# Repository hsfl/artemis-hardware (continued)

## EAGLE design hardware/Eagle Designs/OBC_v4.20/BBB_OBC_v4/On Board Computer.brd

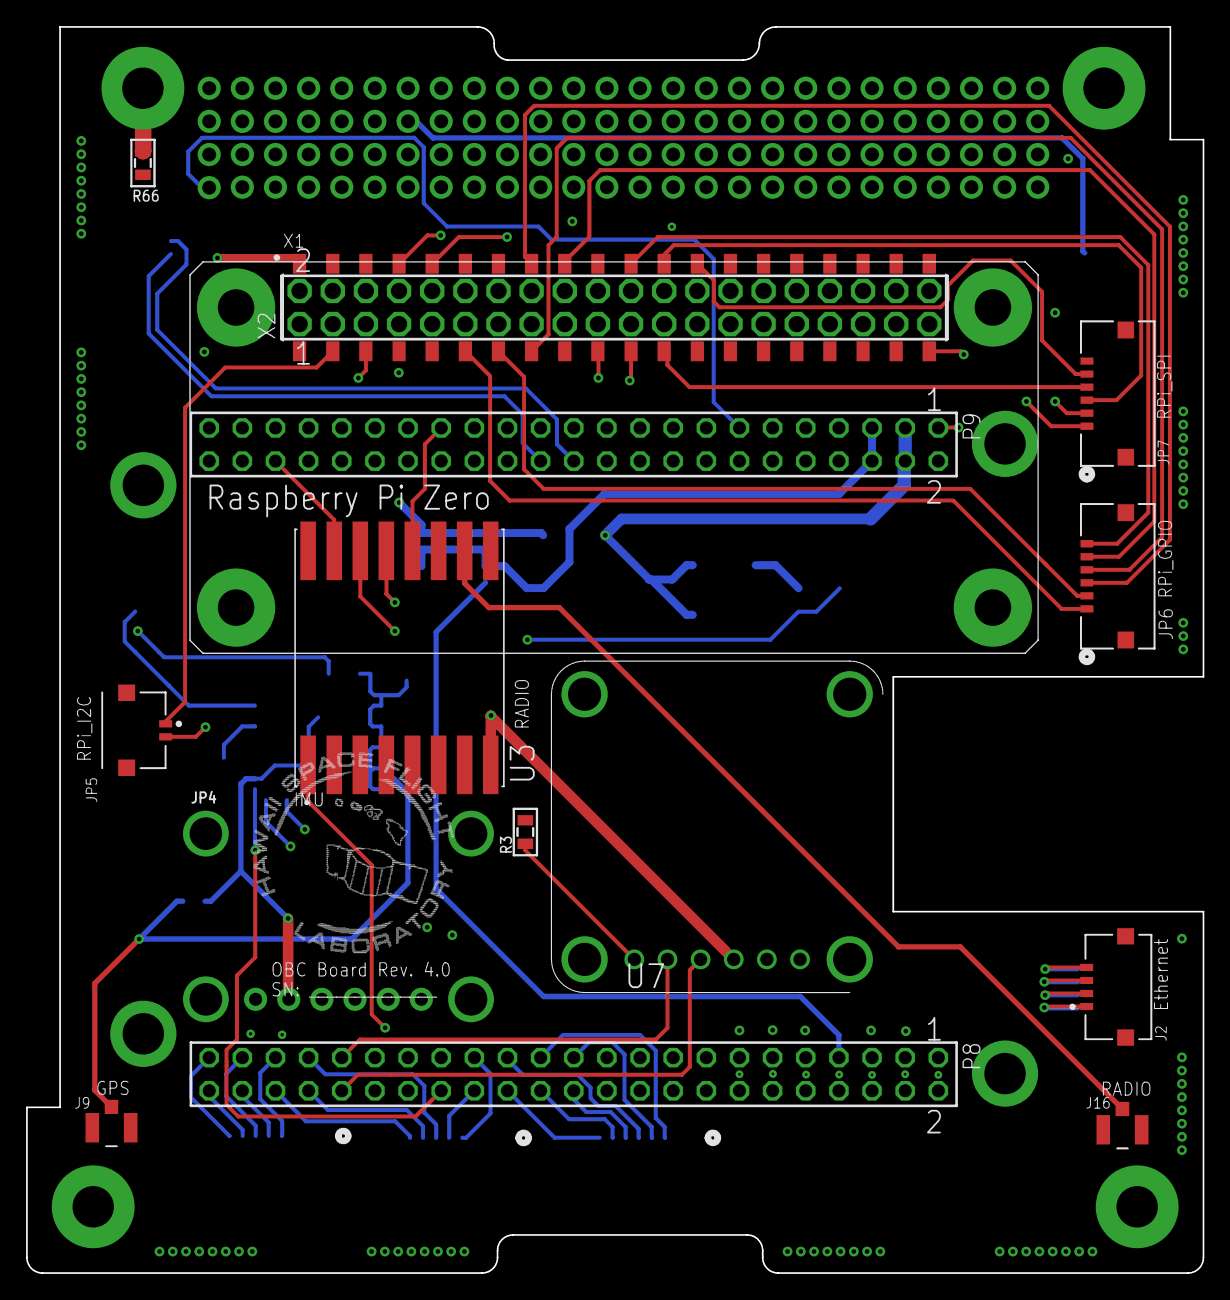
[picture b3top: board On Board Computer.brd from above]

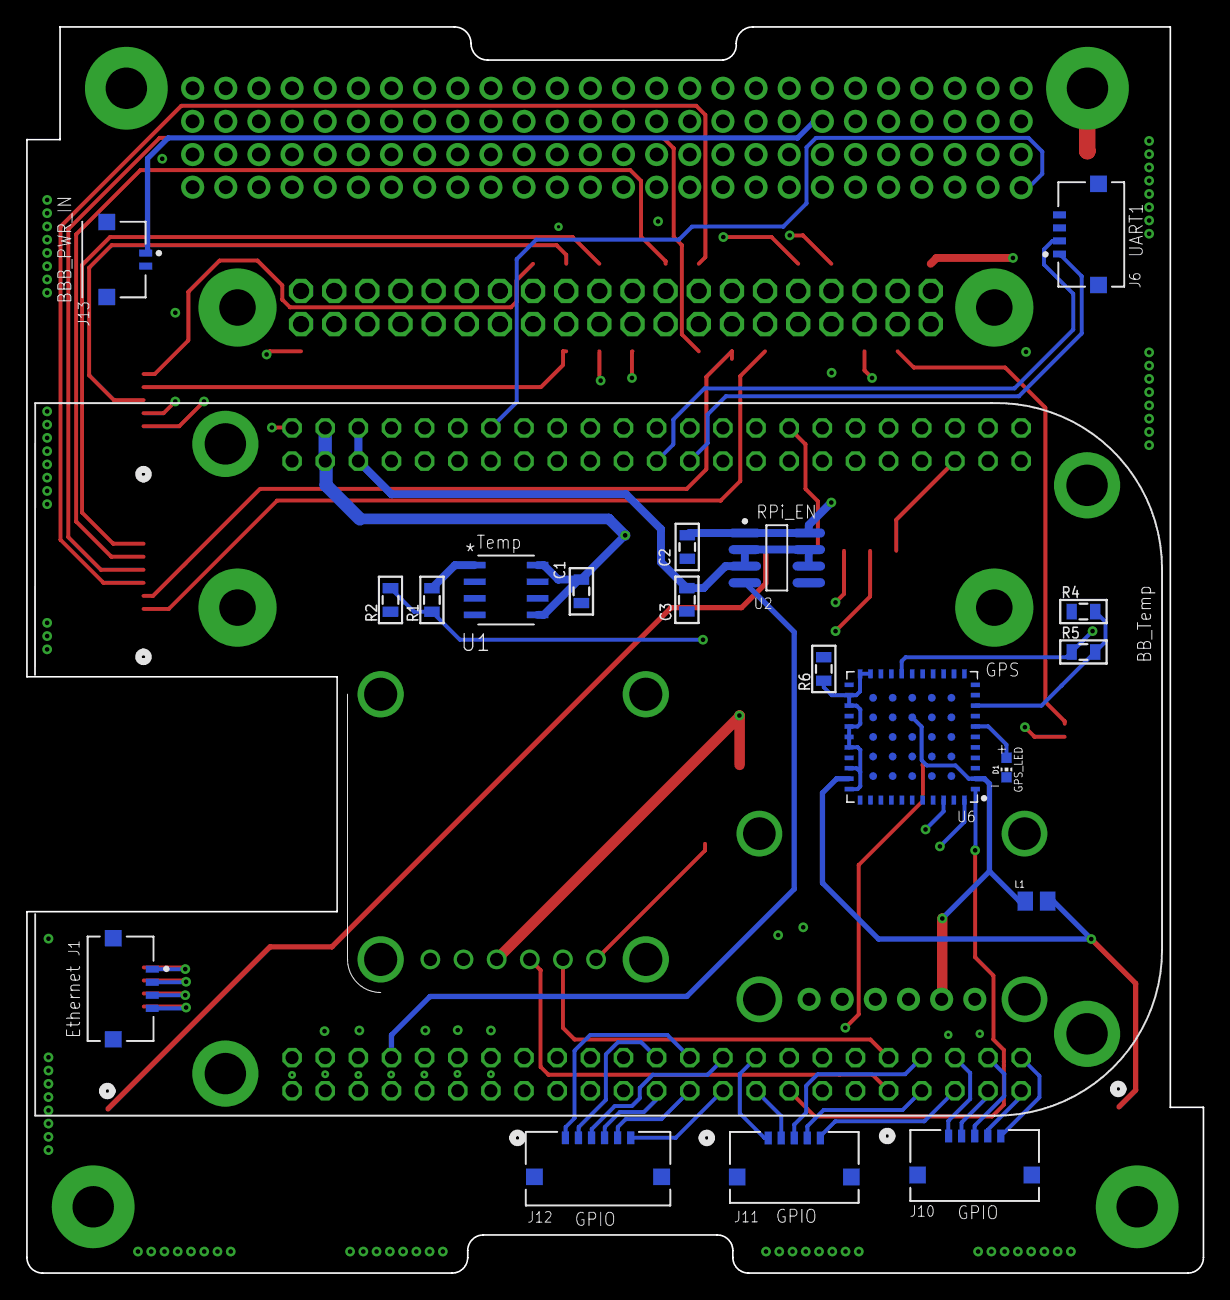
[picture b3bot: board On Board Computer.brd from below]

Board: 4 copper layers, 90.2 x 95.5 mm, 35 parts (19 on the bottom side), 72 nets.

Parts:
C1: .1uF; 0805
C2, C3: 1uF; 0805
D1: CHIP-LED0603
H1: PC104_WCONN
J1, J2, J6: MOLEX_503763-0491MOLEX_503763-0491_0_0; MOLEX_503763-0491_0
J9, J16: U.FL-R-SMT-1(01); CONN_-SMT-1(01)
J10, J11: 503763-0591; CONN_5037630591_MOL
J12: 503763-0691; CONN_503763-0691_MOL
J13: MOLEX_503763-0291MOLEX_503763-0291_0_0; MOLEX_503763-0291_0
JP4: 1X06_ROUND_70
JP5: MOLEX_503763-0291MOLEX_503763-0291_0_0; MOLEX_503763-0291_0
JP6, JP7: 503763-0691; CONN_503763-0691_MOL
L1: L; INDC2012X145N
P8, P9: SSW-123-02-G-D
R1: 27k; 0805
R2, R3: 10k; 0805
R4, R5, R6: 0; 0805
R66: 1M; 0805
U1: TMP36FSZR_8_ADI-L; R_8_ADI-L
U2: LTC1477CS8LINEAR_TECHNOLOGY_LTC1477CS8_0_2; LINEAR_TECHNOLOGY_LTC1477CS8_2
U3: RFM69HCW_433_900; RFM69HCW_433
U6: ORION_A38LORION_A38L; ORION_A38L
U7: PA1010D
X1: C25582-40G-M36-0A; ADAFRUIT_C25582-40G-M36-0A_0
X2: SSW-120-02-G-D

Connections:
3V3_BUS: H1.2.27, H1.2.28, R5.1, U6.18
5V_BUS: H1.2.25, H1.2.26
+3V3_VCC: C1.1, JP4.2, L1.1, P9.3, P9.4, U1.5, U1.8, U3.16, U6.2, U6.58, U7.3
+5V_VCC: C3.1, P9.5, P9.6, U2.2, U2.3, U2.6, U2.7
AIN0: P9.39, R1.1, R2.2
AIN1: H1.1.3, P9.40
AIN2: H1.1.4, P9.37
AIN3: H1.1.5, P9.38
AIN4: H1.1.6, P9.33
AIN5: H1.1.7, P9.36
AIN6: H1.1.8, P9.35
BUS_UART4_RXD(BBB_TX): H1.1.1, P9.13
BUS_UART4_TXD(BBB_RX): H1.1.2, P9.11
GND: C1.2, C2.2, C3.2, D1.C, H1.2.7, H1.2.14, H1.2.17, H1.2.21, H1.2.22, H1.2.29, H1.2.30, H1.2.32, H1.2.47, H1.2.48, J1.5, J1.6, J2.5, J2.6, J6.3, J6.4, J6.5, J6.6, J9.1, J9.2, J10.6, J10.7, J11.6, J11.7, J12.7, J12.8, J13.2, J13.3, J13.4, J16.1, J16.2, JP4.3, JP5.3, JP5.4, JP6.7, JP6.8, JP7.6, JP7.7, JP7.8, P8.1, P8.2, P9.1, P9.2, R2.1, R3.2, R4.1, R6.2, R66.2, U1.4, U2.5, U3.6, U3.8, U6.10, U6.11, U6.15, U6.19, U6.64, U7.1, X1.39
GPIO1_0: J12.1, P8.25
GPIO1_1: J12.4, P8.24
GPIO1_4: J12.2, P8.23
GPIO1_29: J12.5, P8.26
GPIO2_6: J10.5, P8.45
GPIO2_7: J10.4, P8.46
GPIO2_8: J10.3, P8.43
GPIO2_9: J10.2, P8.44
GPIO2_10: J10.1, P8.41
GPIO2_11: J11.5, P8.42
GPIO2_12: J11.3, P8.39
GPIO2_13: J11.4, P8.40
GPIO2_22: J12.3, P8.27
GPIO2_23: J11.1, P8.29
GPIO2_24: J12.6, P8.28
GPIO2_25: J11.2, P8.30
GPIO17: JP6.1, X1.11
GPIO22: JP6.4, X1.15
GPIO23: JP6.3, X1.16
GPIO24: JP6.5, X1.18
GPIO25: JP6.6, X1.22
GPIO27: JP6.2, X1.13
GPS_RSTN: P8.32, U6.1
I2C2_SCL: JP4.4, P9.19
I2C2_SDA: JP4.5, P9.20
unnamed: J16.3, U3.7
unnamed: R1.2, U1.1
unnamed: R4.2, R5.2, U6.9
unnamed: J9.3, L1.2, U6.32
unnamed: R3.1, U7.6
unnamed: D1.A, U6.7
unnamed: H1.P$4, R66.1
RADIO_RESET: P8.36, U3.9
RF_GND: R6.1, U6.21, U6.22, U6.24, U6.25, U6.27, U6.28, U6.29, U6.31, U6.33
RPI_5V_PWR_IN: C2.1, U2.1, U2.8, X1.2
RPI_ENABLE: P8.7, U2.4
RX+: J1.3, J2.2
RX-: J1.4, J2.1
SCL1_I2C: JP5.2, X1.5
SDA1_I2C: JP5.1, X1.3
SPI0_CE0_N: JP7.3, X1.24
SPI0_CE1_N: JP7.5, X1.26
SPI0_MISO: JP7.2, X1.21
SPI0_MOSI: JP7.1, X1.19
SPI0_SCLK: JP7.4, X1.23
SPI1_CS1: P9.42, U3.2
SPI1_D0: P9.29, U3.4
SPI1_D1: P9.30, U3.3
SPI1_SCLK: P9.31, U3.5
SW_5V_1: H1.2.13, J13.1
TX+: J1.1, J2.4
TX-: J1.2, J2.3
UART1_RXD: J6.1, P9.26
UART1_TXD: J6.2, P9.24
UART2_RXD: P9.22, X1.8
UART2_TXD: P9.21, X1.10
UART5_RXD: P8.38, U6.44, U7.4
UART5_TXD: P8.37, U6.42, U7.5

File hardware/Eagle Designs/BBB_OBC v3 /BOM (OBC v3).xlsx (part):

Part | Value | Device | Package | Description | AUTOMOTIVE | AVAILABILITY | BUILT_BY | CENTROID_NOT_SPECIFIED | CIIVA_IDS | COMPONENT_LINK_1_DESCRIPTION | COMPONENT_LINK_1_URL | COMPONENT_LINK_3_DESCRIPTION | COMPONENT_LINK_3_URL | CONN_GENDER | CONN_ORIENTATION | CONTACT_MATERIAL | COPYRIGHT | CURRENT_RATING | DATASHEET | DESCRIPTION | DEVICE_CLASS_L1 | DEVICE_CLASS_L2 | DEVICE_CLASS_L3 | DIGIKEY_DESCRIPTION | DIGIKEY_PART_NUMBER | FOOTPRINT_URL | FOOTPRINT_VARIANT_NAME_0 | FOOTPRINT_VARIANT_NAME_1 | FOOTPRINT_VARIANT_NAME_2 | HEIGHT | IMPORTED | IMPORTED_FROM | IMPORT_TS | LEAD_FREE | MANUFACTURER_PART_NUMBER | MF | MFG_PACKAGE_IDENT | MFG_PACKAGE_IDENT_DATE | MFG_PACKAGE_IDENT_REV | MFR_NAME | MOUNTING_TECHNOLOGY | MOUSER_PART_NUMBER | MP | MPN | NUMBER_OF_CONTACTS | NUMBER_OF_ROWS | OC_FARNELL | OC_NEWARK | PACKAGE | PACKAGE_DESCRIPTION | PACKAGE_VERSION | PITCH | POPULARITY | PREFIX | PRICE | RELEASE_DATE | ROHS | SOURCELIBRARY | TEMPERATURE_RANGE_HIGH | TEMPERATURE_RANGE_LOW | VAULT_GUID | VAULT_REVISION | VENDOR | VERIFICATION_VERSION | VOLTAGE_RATING
3V3_BUS |  | 1,6/0,9 | 1,6/0,9 | THROUGH-HOLE PAD |  |  |  |  |  |  |  |  |  |  |  |  |  |  |  |  |  |  |  |  |  |  |  |  |  |  |  |  |  |  |  |  |  |  |  |  |  |  |  |  |  |  |  |  |  |  |  |  | 7.0
C1 | .1uF | CAP0805 | 805.0 | Capacitor
C2 | 1uF | CAP0805 | 805.0 | Capacitor
C3 | 1uF | CAP0805 | 805.0 | Capacitor
D1 |  | LEDCHIP-LED0603 | CHIP-LED0603 | LED |  |  |  |  |  |  |  |  |  |  |  |  |  |  |  |  |  |  |  |  |  |  |  |  |  |  |  |  |  |  |  |  |  |  |  |  |  |  |  |  |  |  |  |  |  |  |  |  | 26.0
GND | GND | 1,6/0,9 | 1,6/0,9 | THROUGH-HOLE PAD |  |  |  |  |  |  |  |  |  |  |  |  |  |  |  |  |  |  |  |  |  |  |  |  |  |  |  |  |  |  |  |  |  |  |  |  |  |  |  |  |  |  |  |  |  |  |  |  | 7.0
GPS_BOOTSEL |  | 1,6/0,9 | 1,6/0,9 | THROUGH-HOLE PAD |  |  |  |  |  |  |  |  |  |  |  |  |  |  |  |  |  |  |  |  |  |  |  |  |  |  |  |  |  |  |  |  |  |  |  |  |  |  |  |  |  |  |  |  |  |  |  |  | 7.0
H1 | SSQ-126-22-G-D | SSQ-126-22-G-D |  | Large PC104 receptacle |  |  |  |  |  |  |  |  |  |  |  |  |  |  | https://www.mouser.com/datasheet/2/527/ssq_th-1370157.pdf
H2 | SSQ-126-22-G-D | SSQ-126-22-G-D |  | Large PC104 receptacle |  |  |  |  |  |  |  |  |  |  |  |  |  |  | https://www.mouser.com/datasheet/2/527/ssq_th-1370157.pdf
J1 | MOLEX_503763-0491MOLEX_503763-0491_0_0 | MOLEX_503763-0491MOLEX_503763-0491_0_0 | MOLEX_503763-0491_0 | Wire-To-Board Connector, Pico-Lock 503763 Series, Surface Mount, Header, 4 Cont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 | No |  |  | No |  |  |  |  |  | Male | Right Angle | Gold,Nickel |  | 1.5A | https://www.molex.com/webdocs/datasheets/pdf/en-us/503763049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 |  | Connectors | Headers and Wire Housings | unset | CONN HEADER 1MM R/A 4CKT | WM10655CT-ND | https://www.molex.com/pdm_docs/sd/5037630491_sd.pdf | Recommended_Land_Pattern |  |  | 1.7mm |  |  |  | Yes |  | Molex | 503763-0491 | 0.0 | 0.0 |  |  | 538-503763-0491 |  | 503763-0491 | 4.0 | 1.0 |  |  | HDR4 |  |  | 1mm |  | J |  |  | Yes |  | +105°C | -40°C |  |  |  | 0.0.0.1 | 150V
J2 | MOLEX_503763-0491MOLEX_503763-0491_0_0 | MOLEX_503763-0491MOLEX_503763-0491_0_0 | MOLEX_503763-0491_0 | Wire-To-Board Connector, Pico-Lock 503763 Series, Surface Mount, Header, 4 Cont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 | No |  |  | No |  |  |  |  |  | Male | Right Angle | Gold,Nickel |  | 1.5A | https://www.molex.com/webdocs/datasheets/pdf/en-us/503763049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 |  | Connectors | Headers and Wire Housings | unset | CONN HEADER 1MM R/A 4CKT | WM10655CT-ND | https://www.molex.com/pdm_docs/sd/5037630491_sd.pdf | Recommended_Land_Pattern |  |  | 1.7mm |  |  |  | Yes |  | Molex | 503763-0491 | 0.0 | 0.0 |  |  | 538-503763-0491 |  | 503763-0491 | 4.0 | 1.0 |  |  | HDR4 |  |  | 1mm |  | J |  |  | Yes |  | +105°C | -40°C |  |  |  | 0.0.0.1 | 150V
J6 | MOLEX_503763-0491MOLEX_503763-0491_0_0 | MOLEX_503763-0491MOLEX_503763-0491_0_0 | MOLEX_503763-0491_0 | Wire-To-Board Connector, Pico-Lock 503763 Series, Surface Mount, Header, 4 Cont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 | No |  |  | No |  |  |  |  |  | Male | Right Angle | Gold,Nickel |  | 1.5A | https://www.molex.com/webdocs/datasheets/pdf/en-us/503763049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 |  | Connectors | Headers and Wire Housings | unset | CONN HEADER 1MM R/A 4CKT | WM10655CT-ND | https://www.molex.com/pdm_docs/sd/5037630491_sd.pdf | Recommended_Land_Pattern |  |  | 1.7mm |  |  |  | Yes |  | Molex | 503763-0491 | 0.0 | 0.0 |  |  | 538-503763-0491 |  | 503763-0491 | 4.0 | 1.0 |  |  | HDR4 |  |  | 1mm |  | J |  |  | Yes |  | +105°C | -40°C |  |  |  | 0.0.0.1 | 150V
J9 | U.FL-R-SMT-1(01) | U.FL-R-SMT-1(01) | CONN_-SMT-1(01) |  |  |  | EMA_Matt |  |  |  |  |  |  |  |  |  | Copyright (C) 2018 Accelerated Designs. All rights reserved |  |  |  |  |  |  |  |  |  |  |  |  |  |  |  |  |  | U.FL-R-SMT-1(01) |  |  |  |  |  |  |  |  |  |  |  |  |  |  |  |  |  |  |  |  |  |  | Hirose_12_20_2019 |  |  |  |  | Hirose
J10 | 503763-0591 | 503763-0591 | CONN_5037630591_MOL |  |  |  | EMA_Cory |  |  |  |  |  |  |  |  |  | Copyright (C) 2018 Accelerated Designs. All rights reserved |  | https://www.molex.com/pdm_docs/sd/5037630591_sd.pdf |  |  |  |  |  |  |  |  |  |  |  |  |  |  |  | 503763-0591 |  |  |  |  |  |  |  |  |  |  |  |  |  |  |  |  |  |  |  |  |  |  | Add_to_database_2020-12-14 |  |  |  |  | Molex Connector Corporation
J11 | 503763-0591 | 503763-0591 | CONN_5037630591_MOL |  |  |  | EMA_Cory |  |  |  |  |  |  |  |  |  | Copyright (C) 2018 Accelerated Designs. All rights reserved |  | https://www.molex.com/pdm_docs/sd/5037630591_sd.pdf |  |  |  |  |  |  |  |  |  |  |  |  |  |  |  | 503763-0591 |  |  |  |  |  |  |  |  |  |  |  |  |  |  |  |  |  |  |  |  |  |  | Add_to_database_2020-12-14 |  |  |  |  | Molex Connector Corporation
J12 | 503763-0691 | 503763-0691 | CONN_503763-0691_MOL |  |  |  | EMA_Cory |  |  |  |  |  |  |  |  |  | Copyright (C) 2018 Accelerated Designs. All rights reserved |  | https://www.digikey.com/products/en?keywords=503763-0691 |  |  |  |  |  |  |  |  |  |  |  |  |  |  |  | 503763-0691 |  |  |  |  |  |  |  |  |  |  |  |  |  |  |  |  |  |  |  |  |  |  | Molex_2020-01-22 |  |  |  |  | Molex Connector Corporation
J13 | MOLEX_503763-0291MOLEX_503763-0291_0_0 | MOLEX_503763-0291MOLEX_503763-0291_0_0 | MOLEX_503763-0291_0 | 2 Positions Header Connector 0.039 (1.00mm) Surface Mount, Right Angle Gold" |  |  |  | No |  |  |  |  |  |  |  |  |  |  | http://www.molex.com/pdm_docs/sd/5037630291_sd.pdf |  |  |  |  | CONN HEADER 1MM R/A 2CKT | WM10654CT-ND |  |  |  |  |  |  |  |  | yes |  | Molex |  |  |  |  |  | 538-503763-0291 |  | 503763-0291 |  |  |  |  | HDR02 |  |  |  |  | J |  |  | yes |  | +105°C | -40°C
J16 | U.FL-R-SMT-1(01) | U.FL-R-SMT-1(01) | CONN_-SMT-1(01) |  |  |  | EMA_Matt |  |  |  |  |  |  |  |  |  | Copyright (C) 2018 Accelerated Designs. All rights reserved |  |  |  |  |  |  |  |  |  |  |  |  |  |  |  |  |  | U.FL-R-SMT-1(01) |  |  |  |  |  |  |  |  |  |  |  |  |  |  |  |  |  |  |  |  |  |  | Hirose_12_20_2019 |  |  |  |  | Hirose
JP4 | FR20206VBNN | Receptacle | 1X06_ROUND_70 | PIN HEADER |  |  |  |  |  |  |  |  |  |  |  |  |  |  | https://media.metz-connect.com/files/171/Data_sheet_FR202XXVBNN.PDF
JP5 | MOLEX_503763-0291MOLEX_503763-0291_0_0 | MOLEX_503763-0291MOLEX_503763-0291_0_0 | MOLEX_503763-0291_0 | 2 Positions Header Connector 0.039 (1.00mm) Surface Mount, Right Angle Gold" |  |  |  | No |  |  |  |  |  |  |  |  |  |  | http://www.molex.com/pdm_docs/sd/5037630291_sd.pdf |  |  |  |  | CONN HEADER 1MM R/A 2CKT | WM10654CT-ND |  |  |  |  |  |  |  |  | yes |  | Molex |  |  |  |  |  | 538-503763-0291 |  | 503763-0291 |  |  |  |  | HDR02 |  |  |  |  | J |  |  | yes |  | +105°C | -40°C
JP6 | 503763-0691 | 503763-0691 | CONN_503763-0691_MOL |  |  |  | EMA_Cory |  |  |  |  |  |  |  |  |  | Copyright (C) 2018 Accelerated Designs. All rights reserved |  | https://www.digikey.com/products/en?keywords=503763-0691 |  |  |  |  |  |  |  |  |  |  |  |  |  |  |  | 503763-0691 |  |  |  |  |  |  |  |  |  |  |  |  |  |  |  |  |  |  |  |  |  |  | Molex_2020-01-22 |  |  |  |  | Molex Connector Corporation
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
